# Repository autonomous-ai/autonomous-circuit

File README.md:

# Autonomous Circuit: chat with AI → a board you can order

[**Quickstart**](#quickstart) · [How it works](#how-a-board-gets-made) · [The agents](#five-agents-one-job-each) · [The loops](#four-loops-each-one-fixes-a-different-thing) · [Golden blocks](#golden-blocks-compose-never-invent) · [Where it stands](#where-it-actually-stands) · [Contributing](#contributing)

**You describe a gadget. You get back a circuit board you can order.**

Type what you want. Circuit asks a few questions, shows you a plan, and after you say yes it
designs the board and hands you the files a factory needs: the copper layers, the parts list with
part numbers you can actually buy, and where each part goes. Upload those to JLCPCB and the boards
show up in about two weeks.

It's a web app. Chat on the left, the board on the right — schematic, layout, 3D, parts, files.

Two things make it work. Boards are built out of **nine circuits we already know are right**,
rather than made up from datasheets each time. And every board is checked twice, by two programs
that share no code, before anyone is told it's ready.

Here's the catch, up front: nine blocks is not many. Circuit designs the kind of board those blocks
cover — USB-C power, 3.3V logic, an RP2040 chip, I²C sensors, buttons, LEDs. Ask for a motor driver
and it will tell you it can't, instead of guessing.

**That refusal is the point.** A wrong resistor looks exactly like a right one. It looks fine in the
schematic, fine in 3D, fine in every check we run, and fine in the files we send. You find out two
weeks later when the boards arrive and don't work.

---

## Quickstart

Requires Python 3.10+ (3.12 recommended; the system `python3` on a Mac is 3.9 and will not
do — `brew install python@3.12`, or point `CIRCUIT_PYTHON` at one), Node 22.12+ (Vite 7's
floor; `scripts/dev.sh` falls back to Homebrew `node@22` if it is installed), a `claude` CLI
on your PATH, and KiCad for the DRC gate (`brew install --cask kicad`; without it every board
carries a blocking `unverified_gerbers` warning). The app defaults to the Claude arm; the
Codex arm needs Codex.app and a ChatGPT team login.

```bash
git clone https://github.com/autonomous-ai/autonomous-circuit
cd autonomous-circuit
./scripts/dev.sh          # installs the pinned toolchain, starts the app on :4179
```

Open `http://localhost:4179`, pick a starter project, and type what you want. A three-block board
takes about 90 seconds to build; a 400-trace keyboard at maximum router effort takes about 20
minutes.

To build a board from the command line without the app:

```bash
python skills/circuitcode/scripts/circuit boards/main.tsx
# {"ok": true, "fab": {"ready": false}, "warnings": 12, ...}
```

`kicad-cli` is optional but strongly recommended — without it the pipeline still builds, but the
gerbers come from a single exporter with nothing to check them against, and it says so by refusing
to write `ORDER.md`.

---

## How a board gets made

Six steps. Two of them hand the work back.

**You ask, and get a plan.** `circuit-analysis` turns "a coaster that reminds me to drink water"
into a list of what the board actually needs: the parts, how much power, how big. `circuitcode`
turns that into a plan — which blocks, which pin goes where, roughly what it costs. **You approve
the plan before any board exists.** A plan takes a minute to argue with. A finished board takes
twenty.

**Then it writes the board.** Not in a CAD tool — in code. [tscircuit](https://github.com/tscircuit/tscircuit)
is React for circuit boards: parts are elements, wires are props, and the layout gets computed.
This is the trick that makes any of this work. A board written as code is a thing an AI is already
good at.

**Then it gets checked.** Compile the board, then grade it. That's the next section.

**Then it gets reviewed.** Once nothing is broken, seven reviewers look at it. Checks ask "is this
legal?" Reviewers ask "will this actually work, and can we build a hundred of them?"

**Then you get the files.** Circuit only writes the ordering instructions when the board is really
ready to order.

---

## The AI never decides if the board is good

Everything else in this repo follows from that one rule.

An AI writes the board. An AI fixes the board. **No AI ever gets to say the board is fine.** Every
verdict comes from plain code reading the files on disk. The AI's job is to react to what that code
found.

The reason is simple. Ask a model to check its own work and it re-runs the same thinking that
produced the work, so it makes the same mistakes twice and feels confident both times. On a circuit
board you don't catch that. Put a 10Ω resistor where a 10kΩ belongs and the schematic looks right,
the 3D view looks right, every check passes. The board is beautiful and dead.

So Circuit compiles the design once, then grades that one file twice, down two paths that share no
code:

- **Our checks** — read every element, run `@tscircuit/checks`, then measure the board against what
  the factory can actually make: traces and gaps at least 0.127mm, drills at least 0.3mm, copper no
  closer than 0.28mm to a plated hole, and so on.
- **KiCad** — the same design is converted to KiCad files and handed to `kicad-cli`, which runs its
  own checks. KiCad has never heard of tscircuit. When both say a board is clean, two programs with
  different bugs agree.

A third step compares the two versions net by net. A converter that quietly drops a wire would make
the second opinion worthless.

Two rules keep this honest. We learned both the hard way.

**Never trust an exit code.** `tscircuit-cli` exits 0 with real errors in its output. Every check
reads the file it produced, not the return code.

**The files we ship are the files we checked.** The copper layers come out of KiCad, from the same
file KiCad checked. No KiCad installed? Circuit still builds, but it says the files are unverified
and refuses to write the ordering instructions.

---

## Five agents, one job each

The agents are Claude Code skills under `skills/`. Each is a separate context with a separate
system prompt and a narrow job, orchestrated by a Node driver that spawns them as subprocesses. The
shape is the one Anthropic calls
[orchestrator-workers](https://www.anthropic.com/engineering/building-effective-agents).

| Agent | Job | Why it is separate |
|---|---|---|
| **`circuit-analysis`** | vague ask → engineering brief | Interrogating a request and designing a board are different skills. Merged, the model starts designing before it knows what it is designing. |
| **`circuitcode`** | write the board source, run the generator, fix by severity | The only agent that writes TSX. It owns the build-fix cycle and reads the rendered images before calling anything done. |
| **`parts-book`** | lock the BOM to orderable parts | A part that is out of stock is not a part. This resolves every line to an LCSC number against a local mirror of JLCPCB's stocked library. |
| **`design-review`** | score seven lenses, hold the ship bar | Reviewing needs a different prompt from building — and a reviewer that also built it is not a reviewer. |
| **`board-viewer`** | render and explain what is on the board | Serves the app's canvases and the plain-language layer. |

`circuitcode` also ships `circuitlib`, a Python library that owns **every number the agents are
allowed to use** — IPC-2221 trace widths, regulator thermals, LED current, measured block extents,
fab limits. One owner per constant, so a value cannot be right in the planner and wrong in the
checker.

### The panel is seven passes, not one reviewer

`design-review` runs seven lenses — power integrity, manufacturability, layout and signal,
testability, cost and sourcing, safety, product fit — and **each is a separate pass with a separate
question**. They are deliberately not merged: one reviewer looking for everything finds the first
thing and stops. This is
[parallelization by sectioning](https://www.anthropic.com/engineering/building-effective-agents),
and it is the same reason a multi-agent research system beats a single agent with a longer prompt —
[independent contexts do not inherit each other's blind spots](https://www.anthropic.com/engineering/multi-agent-research-system).

Three of the lenses have real arithmetic available and are required to run it. A power lens that
scores by impression will approve a linear regulator dissipating a watt in a SOT-23.

The ship bar: **every lens scores ≥ 7, and no lens has an open must-fix note.** The panel caps at
four rounds. Past that, the design has a problem iteration cannot fix, and the honest move is to
take the disagreement to a human with options.

---

## Four loops, closing over four different things

Feedback is the whole architecture. There are four loops, and they are worth telling apart because
each closes over a different object on a different timescale.

**Loop 1 fixes one build.** Seven checking stages, each reading the files. One of them is a retry:
if the problem looks like bad wire routing, Circuit rebuilds with the router turned up to maximum
and **keeps the second attempt only if it has fewer problems than the first**. On our own boards
that one dial took a keyboard from 46 errors to 18, and a puck from 5 to 1, without changing the
design at all. It costs about 14× the routing time.

**Loop 2 fixes one board.** After a build, Circuit quietly hands the AI everything the checks
found and asks it to fix things — in three passes with hard limits. First anything broken (2 tries),
then anything electrically wrong (3), then anything merely ugly (2). This is
[evaluator-optimizer](https://www.anthropic.com/engineering/building-effective-agents), except the
evaluator is code rather than a model. The limits exist because an AI that can't fix something in
three tries won't fix it in ten.

**Loop 3 fixes one design.** Seven reviewers score it, their must-fix notes go back to
`circuitcode`, and only the reviewers whose subject changed score it again. Four rounds, maximum.

**Loop 4 fixes everything after it.** The first three make *this* board better. The fourth makes
every *future* board better, and it's the one that matters most:

- **Every pair of blocks, built for real** (`evals/composition.py`). Each block passes its own test
  alone. Nobody had ever checked whether they work *together*. The first run: 6 of 42 combinations
  came out clean. The cause was our own placement advice — it recorded each block's *size* and
  assumed the parts sat centred on it. They don't. `usb-c-data`'s copper sits 6.04mm above its
  origin. So every board built on our advice was off by millimetres before anyone wrote a line of
  code.
- **Eight boards it has never seen** (`evals/agent/run.py`). An empty folder, a request, no human
  help, and one question: did the first build come out orderable? Everything else here tests the
  pipeline starting from a board someone already wrote. This tests the actual product.
- **Every bug we ever found, kept forever** (`packages/circuitpy/tests/test_failure_corpus.py`).
  Each one is stored next to the almost-identical case that is legal, so nobody can "fix" a bug by
  quietly moving a threshold.

The rule tying Loop 4 to the rest: **when a board fails and the AI fixes it, ask why the first
attempt got it wrong, and fix that instead.** The fix belongs in the block, the starting template,
or the planner — never in a note someone has to remember. A block that needs careful handling to be
safe is a block that will get handled wrong.

`docs/lessons.md` tracks this. Every defect we've hit, and where the fix landed. Detecting a
problem doesn't count as fixing it, so those entries stay open until the problem becomes
impossible.

### Why we can afford to check this hard

Miss something and you wait two weeks for new boards. That's not just lost time, it's lost market.
Against that, almost any amount of checking is cheap — so the budget is **days of compute**.

That only works if the checking runs in parallel. `batch.py` runs builds across every core and
reports two numbers separately: compute spent, and time you actually waited. The second is the one
that matters.

---

## Golden blocks: compose, never invent

A golden block is a small circuit that someone checked once and then froze — the part values, which
way round things go, which pin is which, the pad shapes. Nine exist: USB-C power, USB-C with data,
a 3.3V regulator, an I²C bus, a status LED, a button, an RP2040 core, a BME280 sensor, and a
WS2812 LED chain.

Each ships a `BLOCK.md` datasheet — pin contract, rail budget, pinned LCSC parts with a verification
date, provenance — and a graded testbench that builds it as a **real board** through the real
pipeline, with routing on and production board constraints applied. A block that would block any
board built from it fails its own test, named after itself.

This exists because of the gap two sections up. No check catches a wrong value or a flipped pinout,
because everything we render comes from the same source — if the source is wrong, everything agrees
with it. Freezing the values removes that whole class of bug. The checks then cover what putting
blocks *together* can break.

Ask for something we don't have a block for and Circuit says so. That's a real answer, not a
failure.

### The safety envelope

Refused at spec time, in the plan, before any toolchain process runs:

- **No mains voltage, ever.** Low-voltage DC ≤ 24V only.
- **Battery power only through a sealed, validated charge/protect block.** None exists yet — the
  slot is deliberately empty rather than filled with something plausible.
- **Radio only as certified modules.**

---

## Where it actually stands

v1, in active development, and the honest numbers move daily. As of 2026-08-11:

- **Composition closure: 56%** of legal block combinations build clean, up from 14% before the
  placement fix above. The guarantee we are building toward is closure — if every block is clean
  alone and every combination is clean, then "any board a user can reach is fab-ready" stops being a
  hope about the future and becomes a property of the library. 56% is not that yet.
- **The three example boards are not orderable.** All three fail on USB-C shell plated-hole
  clearance, and one has an unconnected rail. The current state of each is in
  `examples/*/boards/main.board.json`.

We publish these because a fab-ready rate you cannot see is a fab-ready rate you cannot trust. The
bar itself does not move to meet the number: `fab.ready` requires zero error-severity findings **and**
gerbers independently verified by `kicad-cli`. Loosening that to improve the statistic would destroy
the only thing that makes the statistic worth having.

---

## Repo layout

```
viewer/            the web app — Vite + React chat and board workspace,
                   plus the Node driver that spawns the agents
  src/server/      driver (turns, review loop), HTTP commands, projects, JLCPCB client
  src/client/      canvases, findings, plain-language layer
packages/
  circuitpy/       the pipeline: source → compile → verify → fab packet
  golden-blocks/   the validated subcircuits, each with BLOCK.md + a testbench
  parts-catalog/   local mirror of JLCPCB's stocked library
  verify/          deeper verification — SPICE, gerber truth
skills/            the agents (SKILL.md each) + circuitlib, the number owner
evals/             composition matrix, cold-brief agent eval
examples/          real product boards — Hydrate coaster, Harness puck, Terminal
                   keyboard. Each folder has the board, its gerbers, BOM, KiCad
                   project and a REVIEW.md; examples/README.md is the packet we
                   send an engineer before release
docs/              circuit-interfaces.md is the frozen contract; changes are append-only
toolchain/         pinned tscircuit, exact version
```

**`docs/circuit-interfaces.md` is the contract** between the pipeline, the server and the skills.
It is frozen: changes go through the append-only `-CHANGES.md` beside it. Read it before changing
anything that crosses those boundaries.

---

## Contributing

The most useful contributions, roughly in order:

1. **A golden block.** The catalog is the bottleneck on what can be designed. A block needs a
   `BLOCK.md`, pinned LCSC parts, and a testbench that passes the full gauntlet as a real board.
   A buck regulator, a motor driver and a battery charge/protect block are all wanted.
2. **A check that catches something real.** Add it with a failure-corpus entry: the defect, and the
   legal geometry just the other side of the line.
3. **A fab profile.** Everything fab-specific lives in one limit table (`circuitpy/fab.py`). JLCPCB
   is the only profile today; PCBWay and OSH Park are the same shape of work.

Run the tests before opening a PR:

```bash
PYTHONPATH=packages/circuitpy/src python -m pytest packages/circuitpy/tests -q
cd skills/circuitcode && PYTHONPATH=. python -m pytest tests -q
npm --prefix viewer test
scripts/shift-left-check     # every fix the defect ledger claims is still in the tree
```

Two conventions that are not negotiable, both above: no gate may trust an exit code, and no fix may
live in advice a user has to remember.

---

Built by [Autonomous](https://autonomous.ai). Licensed under the [MIT License](LICENSE).

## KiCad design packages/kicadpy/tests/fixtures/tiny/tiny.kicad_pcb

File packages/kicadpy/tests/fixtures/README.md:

# Native repair fixtures

`tiny/` is an original, synthetic 30 × 20 mm, two-net project authored for
this test suite. Four through-hole test points and two straight tracks put
SIGNAL across OTHER's pad, creating a deliberate short/clearance violation.
Moving SIGNAL above the pad fixes the defect without changing OTHER.
The schematic, project symbols and footprint are local; no network is needed.
It is a test board, not a fabrication design.

`native-route.ses` was captured on 2026-09-15 using native KiCad 10.0.5 DSN
export and Freerouting 2.4.1 (`-mp 5 -mt 1`). Trailing whitespace is removed.
The protected OTHER track is intentionally absent from the SES. Replaying it
checks that the native importer restores the original protected object and
keeps its UUID and geometry. Tests do not launch Freerouting or use a network.

The separate Desk Cube smoke script accepts a local release path, copies it
to a temporary directory and never commits or mutates that source design.

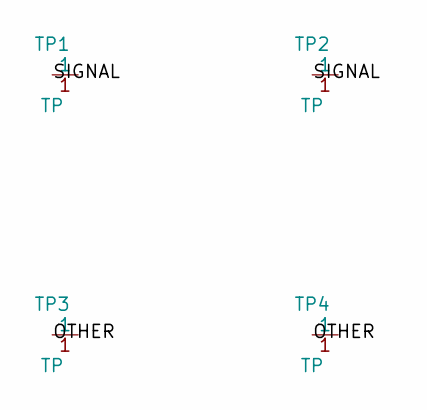
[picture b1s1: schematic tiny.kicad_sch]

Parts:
TP1, TP2, TP3, TP4: TP

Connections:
/OTHER: TP3.1, TP4.1
/SIGNAL: TP1.1, TP2.1

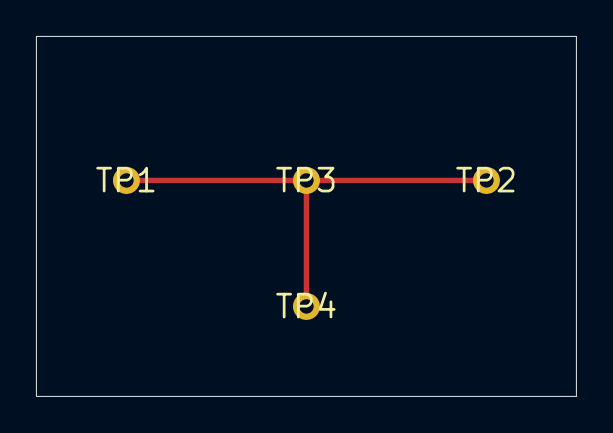
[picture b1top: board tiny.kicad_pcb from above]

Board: 2 copper layers, 30.0 x 20.0 mm, 4 parts (0 on the bottom side), 2 nets.

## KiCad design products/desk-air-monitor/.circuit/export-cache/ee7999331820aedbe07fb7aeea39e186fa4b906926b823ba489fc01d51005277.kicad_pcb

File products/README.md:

# The fleet

Boards built **with the app**, by the AI electrical engineers who are testing
it. `examples/` holds the three the test suite pins; this holds everything
after that, and it exists for one reason:

> Three boards prove the pipeline can build a board. Tens of boards prove the
> tool is ready for someone else's hands.

Every product here is a real device someone might order — not a demo, not a
skeleton — and every one carries the same verdict the first three do.

## The bar

A product is **done** when its sidecar says `"fab": {"ready": true}` with zero
blocking findings, and the fab packet under `boards/main_fab/` is complete
(gerbers, BOM, CPL, ORDER.md). Anything short of that stays in the table below
with its real state, because a fleet that only lists its successes measures
nothing.

`fab.ready: true` is a **floor**. A later build may never report `false` after
a `true`; the change that did it gets reverted and the finding recorded.

## How one gets built

```bash
SKILL=~/.claude/skills/circuitcode
mkdir -p products/<slug>
cp -R "$SKILL/templates/project_skeleton/." products/<slug>/
cp -R "$SKILL/blocks" products/<slug>/blocks
# edit products/<slug>/product.json first — name, power, envelopeMm, layers
# then write products/<slug>/boards/main.tsx from the golden blocks
/Users/d/miniconda/bin/python3.12 "$SKILL/scripts/circuit" \
    /Users/d/code/autonomous-circuit/products/<slug>/boards/main.tsx
```

Read the verdict off the last line of stdout (one JSON object) and then off
`boards/main.board.json` → `validation.warnings[]` by severity. **Look at both
review PNGs** before calling anything finished.

The golden blocks are the vocabulary: `usb-c-power`, `usb-c-data`, `ldo-3v3`,
`rp2040-core`, `status-led`, `sw-tact`, `ws2812-chain`, `sensor-bme280`,
`i2c-bus`, plus `glue.tsx` (mounting holes, pours). A product that needs
something outside that list is a **finding about the library**, not a reason to
invent a circuit inline.

## What the builders owe us besides the board

Every engineer who builds one writes down where the tool got in their way, in
`work/ee-feedback/<slug>.md`: what they reached for that was not there, what
they had to do by hand, what the app told them that turned out to be wrong.
That file is the input to the next round of IDE work — the boards are the
product, the friction is the point.

## The fleet

| Product | What it is | `fab.ready` | Blocking | In the app | Notes |
|---|---|---|---|---|---|
| `bench-i2c-scanner` | USB-C bench tool that enumerates every device on an I2C bus and report | no | 3 | no (3) | 91.9 × 63.8mm · 2× drc_violation, 1× dfm_hole_clearance |
| `desk-air-monitor` | USB-C desk device that reads temperature, humidity and pressure and sh | **yes** | 0 | **yes** | 61 × 64.8mm · ⚠ source is newer than this verdict |
| `dual-rail-psu` | USB-C bench supply brick: 5V and 3V3 broken out on labelled pad header | **yes** | 0 | **yes** | 41.1 × 51mm |
| `dual-sensor-node` | USB-C RP2040 node with two BME280s on one I2C bus (on-board + short pi | **yes** | 0 | **yes** | 95.3 × 68mm |
| `env-logger-usb` | USB-C environment logger that streams temperature, humidity and pressu | **yes** | 0 | **yes** | 99.6 × 64mm |
| `i2c-sensor-hub` | USB-C board that reads a BME280 and breaks its I2C bus out to a pad he | **yes** | 0 | **yes** | 95 × 67mm |
| `macropad-6` | USB-C six-key macropad: 3x2 grid of tactile switches on 19 | no | 10 | no (10) | 66 × 84mm · 6× drc_violation, 3× pcb_via_trace_clearance_error |
| `pixel-badge` | a wearable conference badge: 8 addressable RGB pixels across the top,  | no | 9 | no (9) | 82 × 58mm · 6× drc_violation, 2× pcb_via_trace_clearance_error |
| `rgb-lamp-controller` | USB-C desk lamp controller: RP2040 brain driving 8 on-board WS2812 pix | **yes** | 0 | **yes** | 84.9 × 68.6mm |
| `sensor-node-mini` | Small always-on environment node: temperature, humidity and pressure o | **yes** | 0 | **yes** | 80.9 × 45.9mm · ⚠ source is newer than this verdict |
| `two-key-footswitch` | USB-C RP2040 footswitch with two heavy-press keys for push-to-talk and | **yes** | 0 | **yes** | 47.5 × 68.9mm |
| `usb-c-breakout` | USB-C receptacle broken out to labelled bench pads (VBUS, GND, CC1, CC | **yes** | 0 | **yes** | 36 × 40.5mm |

**9 of 12 built boards are fab-ready** (12 products in the fleet).

**In the app a human actually opens: 9 of 12.** The repo is not the product — these are the same boards as installed under `~/.autonomous-circuit/projects/`, and the two numbers parting company is a finding, not a rounding. `scripts/install-fleet` closes the gap.

**Verdict older than its own source**: `desk-air-monitor`, `sensor-node-mini` — the board was edited and never rebuilt, so its numbers describe a board that no longer exists (ledger #42).

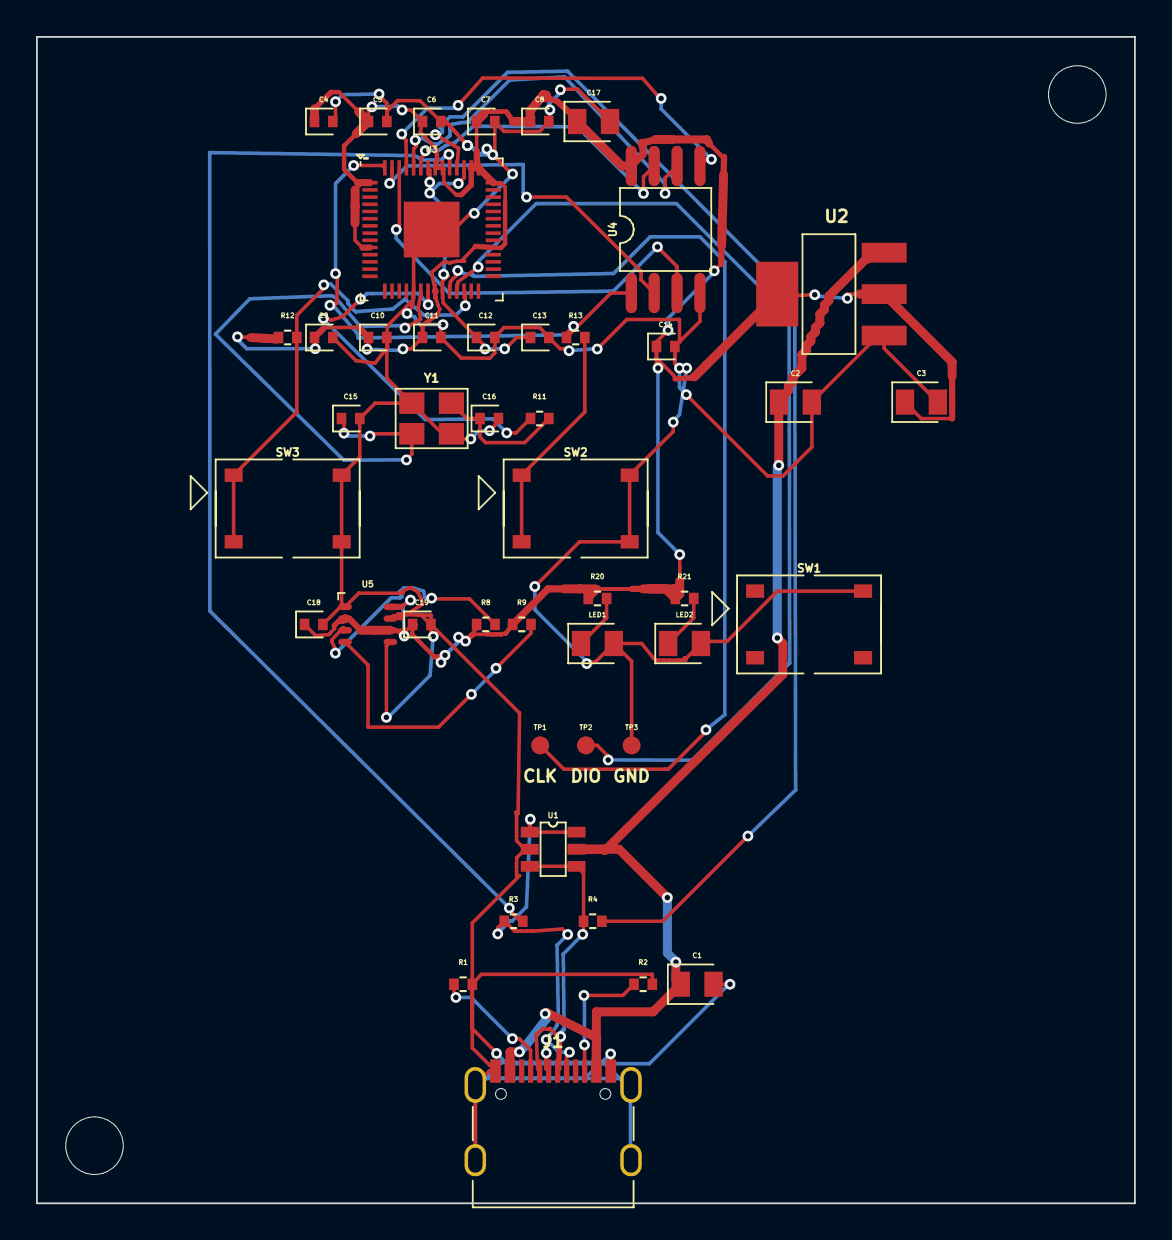
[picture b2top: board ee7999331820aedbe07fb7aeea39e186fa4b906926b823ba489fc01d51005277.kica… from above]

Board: 2 copper layers, 61.0 x 64.8 mm, 45 parts (0 on the bottom side), 27 nets.

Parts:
C1, C2, C3, C17: 10uF; capacitor_cap0805
C4, C5, C6, C7, C8, C9, C10, C11, C13, C14, C18, C19: 100nF; capacitor_cap0402
C12: 1uF; capacitor_cap0402
C15, C16: 15pF; capacitor_cap0402
J1: J1; TYPE-C-31-M-12
LED1, LED2: LED; led_0805_color(green)
R1, R2: 5.1kΩ; resistor_res0402
R3, R4: 27Ω; resistor_res0402
R8, R9: 4.7kΩ; resistor_res0402
R11, R13, R20, R21: 1kΩ; resistor_res0402
R12: 10kΩ; resistor_res0402
SW1: SW1; push_button_dfn4_p3.6998mm_w7mm_pw0.75mm
SW2: SW2; push_button_dfn4_p3.6998mm_w7mm_pw0.75mm
SW3: SW3; push_button_dfn4_p3.6998mm_w7mm_pw0.75mm
TP1: TP1; test_point_smtpad_circle_d1
TP2: TP2; test_point_smtpad_circle_d1
TP3: TP3; test_point_smtpad_circle_d1
U1: USBLC6-2SC6
U2: AMS1117-3.3
U3: RP2040
U4: W25Q128JVSIQ
U5: BME280
Y1: Y1; crystal_crystal

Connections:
.J1 > .CC1 to .R1 > .pin1: J1.6, R1.1
.J1 > .CC2 to .R2 > .pin1: J1.12, R2.1
.R11 > .pin2 to .Y1 > .pin3: C16.1, R11.2, Y1.3
.R20 > .pin2 to .LED1 > .anode: LED1.1, R20.2
.R21 > .pin2 to .LED2 > .anode: LED2.1, R21.2
.U3 > .XOUT to .R11 > .pin1: R11.1, U3.21
.U4 > .CLK to .U3 > .QSPI_SCLK: U3.52, U4.6
.U4 > .CS to .U3 > .QSPI_SS: R13.1, U3.56, U4.1
.U4 > .IO0 to .U3 > .QSPI_SD0: U3.53, U4.5
.U4 > .IO1 to .U3 > .QSPI_SD1: U3.55, U4.2
.U4 > .IO2 to .U3 > .QSPI_SD2: U3.54, U4.3
.U4 > .IO3 to .U3 > .QSPI_SD3: U3.51, U4.7
.Y1 > .pin1 to .U3 > .XIN: C15.1, U3.20, Y1.1
BOOTSEL_SW: R13.2, SW2.1, SW2.2
DVDD: C12.1, C13.1, U3.23, U3.45, U3.50
GND: C1.2, C2.2, C3.2, C4.2, C5.2, C6.2, C7.2, C8.2, C9.2, C10.2, C11.2, C12.2, C13.2, C14.2, C15.2, C16.2, C17.2, C18.2, C19.2, J1.1, J1.2, J1.3, J1.4, J1.13, J1.14, LED1.2, LED2.2, R1.2, R2.2, SW1.4, SW2.3, SW2.4, SW3.3, SW3.4, TP3.1, U1.2, U2.1, U3.19, U3.57, U4.4, U5.1, U5.5, U5.7, Y1.2, Y1.4
RUN_SW: R12.2, SW3.1, SW3.2, U3.26
SCL: R9.2, U5.4
SDA: R8.2, U5.3
SWCLK: TP1.1, U3.24
SWD: TP2.1, U3.25
USB_DM: R4.2, U3.46
USB_DM_CONN: J1.7, J1.9, R4.1, U1.3, U1.4
USB_DP: R3.2, U3.47
USB_DP_CONN: J1.8, J1.10, R3.1, U1.1, U1.6
V3_3: C3.1, C4.1, C5.1, C6.1, C7.1, C8.1, C9.1, C10.1, C11.1, C14.1, C17.1, C18.1, C19.1, R8.1, R9.1, R12.1, R20.1, R21.1, U2.2, U2.4, U3.1, U3.10, U3.22, U3.33, U3.42, U3.43, U3.44, U3.48, U3.49, U4.8, U5.2, U5.6, U5.8
V5: C1.1, C2.1, J1.15, J1.16, U1.5, U2.3

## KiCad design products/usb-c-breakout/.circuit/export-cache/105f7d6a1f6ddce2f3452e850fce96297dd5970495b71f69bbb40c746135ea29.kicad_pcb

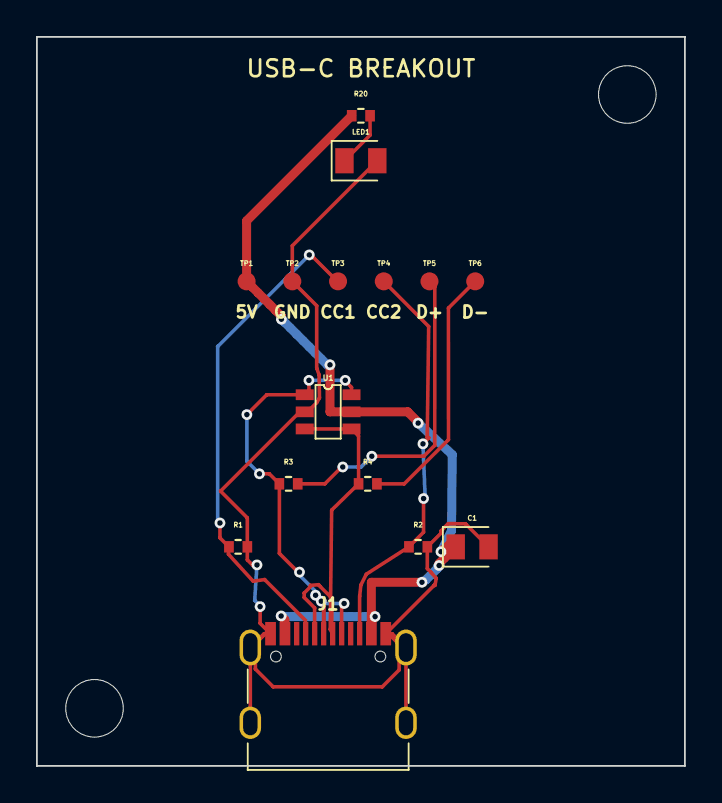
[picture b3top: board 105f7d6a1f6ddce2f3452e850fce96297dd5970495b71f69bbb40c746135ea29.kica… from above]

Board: 2 copper layers, 36.0 x 40.5 mm, 15 parts (0 on the bottom side), 9 nets.

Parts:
C1: 10uF; capacitor_cap0805
J1: J1; TYPE-C-31-M-12
LED1: LED; led_0805_color(green)
R1, R2: 5.1kΩ; resistor_res0402
R3, R4: 27Ω; resistor_res0402
R20: 1kΩ; resistor_res0402
TP1: TP1; test_point_smtpad_circle_d1
TP2: TP2; test_point_smtpad_circle_d1
TP3: TP3; test_point_smtpad_circle_d1
TP4: TP4; test_point_smtpad_circle_d1
TP5: TP5; test_point_smtpad_circle_d1
TP6: TP6; test_point_smtpad_circle_d1
U1: USBLC6-2SC6

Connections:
.J1 > .CC1 to .R1 > .pin1: J1.6, R1.1, TP3.1
.J1 > .CC2 to .R2 > .pin1: J1.12, R2.1, TP4.1
.R20 > .pin2 to .LED1 > .anode: LED1.1, R20.2
GND: C1.2, J1.1, J1.2, J1.3, J1.4, J1.13, J1.14, LED1.2, R1.2, R2.2, TP2.1, U1.2
USB_DM: R4.2, TP6.1
USB_DM_CONN: J1.7, J1.9, R4.1, U1.3, U1.4
USB_DP: R3.2, TP5.1
USB_DP_CONN: J1.8, J1.10, R3.1, U1.1, U1.6
V5: C1.1, J1.15, J1.16, R20.1, TP1.1, U1.5

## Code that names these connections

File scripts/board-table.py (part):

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        xout = alias.get(("U3", "xout"))
        _, ss_pins, _ = on("U3", "QSPI_SS")
        _, run_pins, _ = on("U3", "RUN")
        _, dp_pins, _ = on("U3", "USB_DP")
        _, dm_pins, _ = on("U3", "USB_DM")
        _, swclk_pins, _ = on("U3", "SWCLK")
        results = [
            rail in ("V3_3", "V5")
            and vin_root != vout_root
            and any(r == "U3" and p.startswith("DVDD") for r, p in vout_pins),
            xin is not None and xout is not None and xin != xout
            and any(r.startswith("Y") for r, _ in xin_pins),
            all(
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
